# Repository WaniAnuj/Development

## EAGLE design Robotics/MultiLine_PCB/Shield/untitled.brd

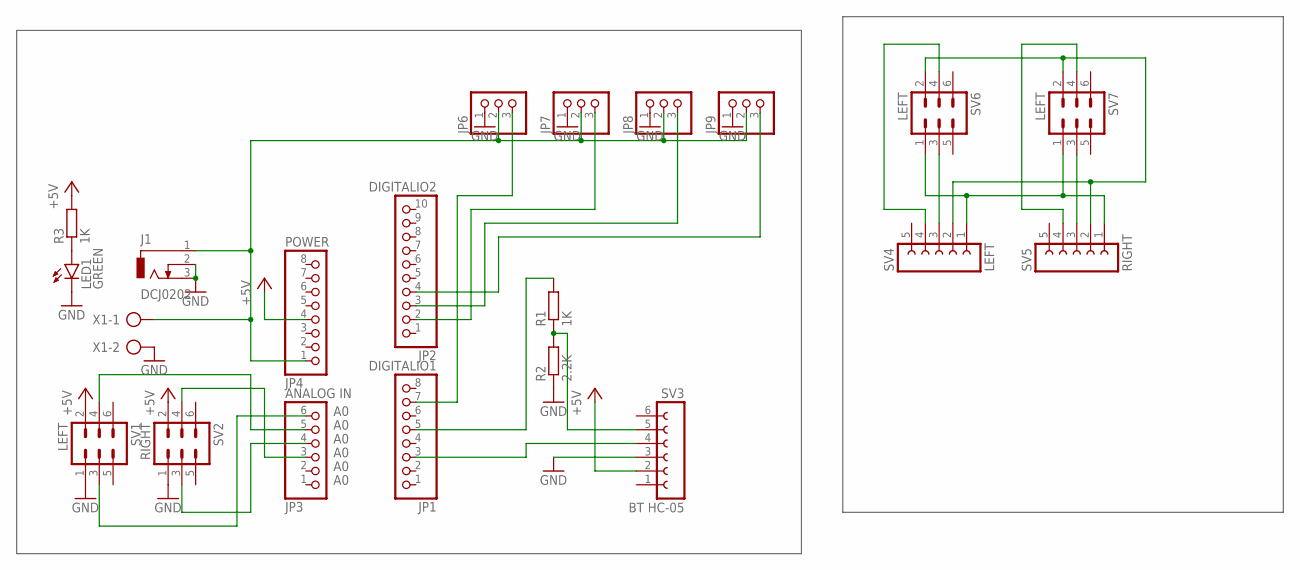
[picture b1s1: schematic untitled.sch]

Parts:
J1: DCJ0202
JP1: DIGITALIO1; 1X08
JP2: DIGITALIO2; 1X10
JP3: ANALOG IN; 1X06
JP4: POWER; 1X08
JP6, JP7, JP8, JP9: PINHD-1X3; 1X03
LED1: GREEN; LED3MM
R1, R3: 1K; 0207/10
R2: 2.2K; 0207/10
SV1, SV6, SV7: LEFT; ML6
SV2: RIGHT; ML6
SV3: BT HC-05; FE06W
SV4: LEFT; FE05W
SV5: RIGHT; FE05W
X1: AK300/2

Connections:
+5V: JP4.4, R3.2, SV1.2, SV2.2, SV3.2
GND: J1.2, J1.3, JP6.1, JP7.1, JP8.1, JP9.1, LED1.K (C), R2.1, SV1.1, SV2.1, SV3.3, X1.2
unnamed: JP1.3, SV3.4
unnamed: J1.1, JP4.1, JP6.2, JP7.2, JP8.2, JP9.2, X1.1
unnamed: R1.1, R2.2, SV3.5
unnamed: JP1.5, R1.2
unnamed: JP3.6, SV1.3
unnamed: JP1.7, JP6.3
unnamed: JP2.2, JP7.3
unnamed: JP2.3, JP8.3
unnamed: JP2.4, JP9.3
unnamed: JP3.5, SV1.4
unnamed: JP3.4, SV2.3
unnamed: JP3.3, SV2.4
unnamed: LED1.A, R3.1
unnamed: SV4.1, SV5.1, SV6.1, SV7.1
unnamed: SV4.2, SV5.2, SV6.2, SV7.2
unnamed: SV4.3, SV6.3
unnamed: SV4.4, SV6.4
unnamed: SV5.3, SV7.3
unnamed: SV5.4, SV7.4

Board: 2 copper layers, 21 parts (0 on the bottom side), 21 nets, no tracks yet.

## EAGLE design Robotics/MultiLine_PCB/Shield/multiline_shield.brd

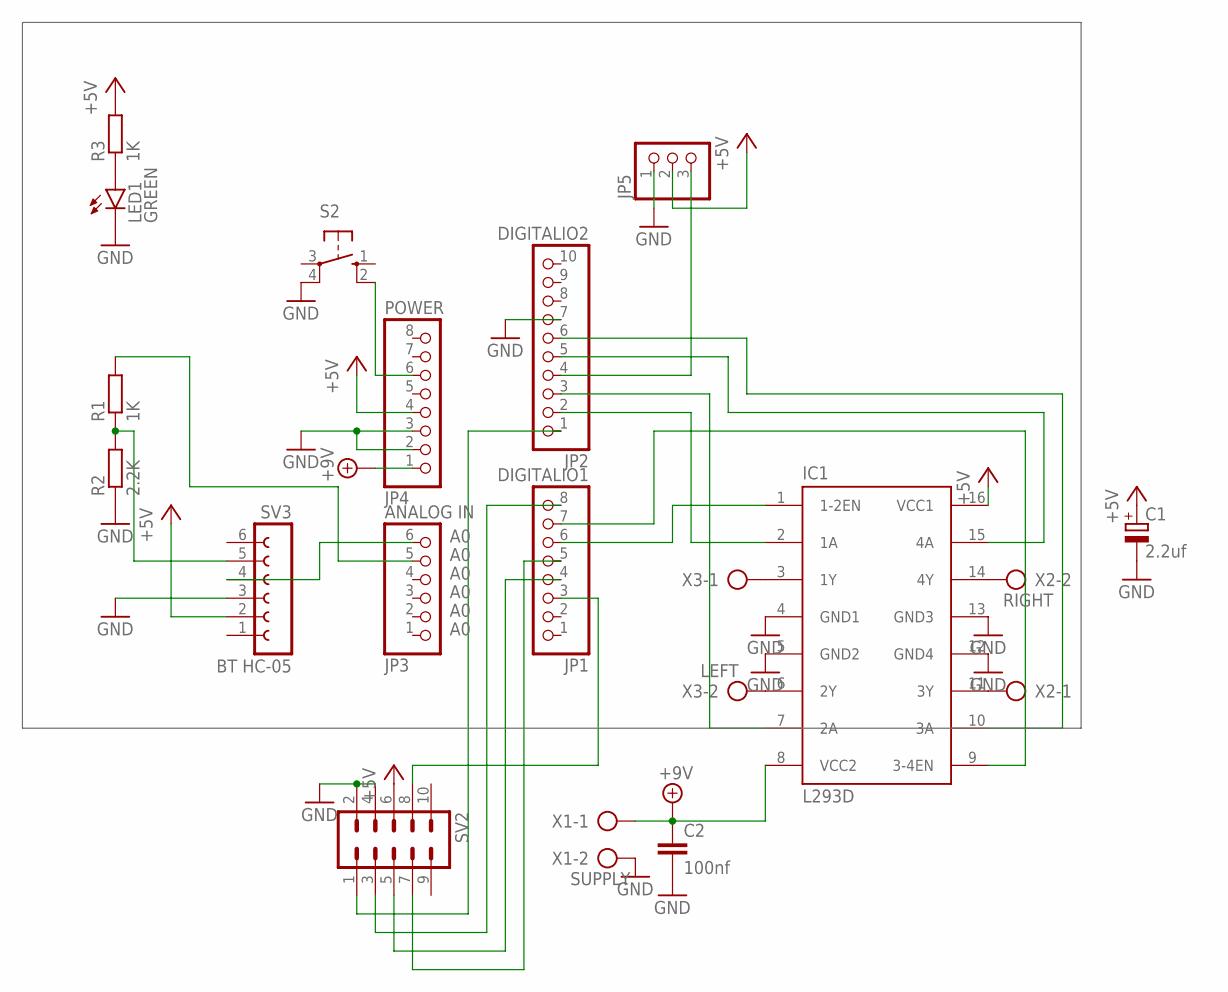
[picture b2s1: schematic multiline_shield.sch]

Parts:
C1: 2.2uf; E2,5-6
C2: 100nf; C025-025X050
IC1: L293D; DIL16
JP1: DIGITALIO1; 1X08
JP2: DIGITALIO2; 1X10
JP3: ANALOG IN; 1X06
JP4: POWER; 1X08
JP5: PINHD-1X3; 1X03
LED1: GREEN; LED3MM
R1, R3: 1K; 0207/10
R2: 2.2K; 0207/10
S2: 10-XX; B3F-10XX
SV2: ML10
SV3: BT HC-05; FE06
X1: SUPPLY; AK300/2
X2: RIGHT; AK300/2
X3: LEFT; AK300/2

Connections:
+5V: C1.+, IC1.16 (VCC1), JP4.4, JP5.2, R3.2, SV2.6, SV3.2
+9V: C2.1, IC1.8 (VCC2), JP4.1, X1.1
GND: C1.-, C2.2, IC1.4 (GND1), IC1.5 (GND2), IC1.12 (GND4), IC1.13 (GND3), JP2.7, JP4.2, JP4.3, JP5.1, LED1.K (C), R2.1, S2.4 (P1), SV2.2, SV2.4, SV3.3, X1.2
unnamed: JP3.6, SV3.4
unnamed: JP4.6, S2.2 (S1)
unnamed: R1.1, R2.2, SV3.5
unnamed: JP3.5, R1.2
unnamed: IC1.2 (1A), JP2.2
unnamed: JP2.4, JP5.3
unnamed: IC1.7 (2A), JP2.3
unnamed: IC1.1 (1-2EN), JP1.6
unnamed: IC1.15 (4A), JP2.5
unnamed: IC1.10 (3A), JP2.6
unnamed: IC1.9 (3-4EN), JP1.7
unnamed: IC1.11 (3Y), X2.1
unnamed: LED1.A, R3.1
unnamed: IC1.14 (4Y), X2.2
unnamed: IC1.3 (1Y), X3.1
unnamed: IC1.6 (2Y), X3.2
unnamed: JP2.1, SV2.1
unnamed: JP1.8, SV2.3
unnamed: JP1.4, SV2.5
unnamed: JP1.5, SV2.7
unnamed: JP1.3, SV2.8

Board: 2 copper layers, 18 parts (0 on the bottom side), 24 nets, no tracks yet.

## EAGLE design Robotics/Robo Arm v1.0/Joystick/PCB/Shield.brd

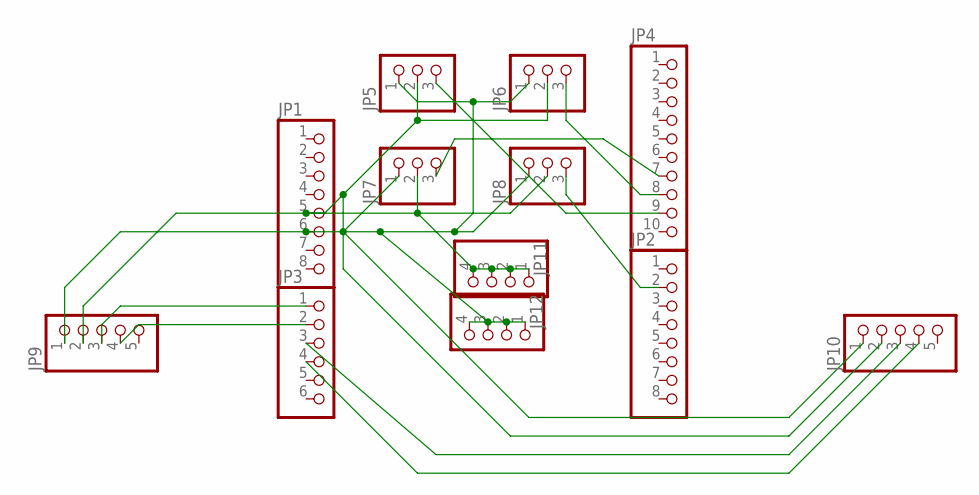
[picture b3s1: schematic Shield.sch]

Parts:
JP1, JP2: PINHD-1X8; 1X08
JP3: PINHD-1X6; 1X06
JP4: PINHD-1X10; 1X10
JP5, JP6, JP7, JP8: PINHD-1X3; 1X03
JP9, JP10: PINHD-1X5; 1X05
JP11, JP12: PINHD-1X4; 1X04

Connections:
GND: JP1.6, JP5.1, JP6.1, JP7.1, JP8.1, JP9.1, JP10.1, JP12.1, JP12.2, JP12.3, JP12.4
unnamed: JP1.5, JP5.2, JP6.2, JP7.2, JP8.2, JP9.2, JP10.2, JP11.1, JP11.2, JP11.3, JP11.4
unnamed: JP4.9, JP5.3
unnamed: JP3.1, JP9.3
unnamed: JP4.8, JP6.3
unnamed: JP3.2, JP9.4
unnamed: JP3.3, JP10.3
unnamed: JP3.4, JP10.4
unnamed: JP2.2, JP8.3
unnamed: JP4.7, JP7.3

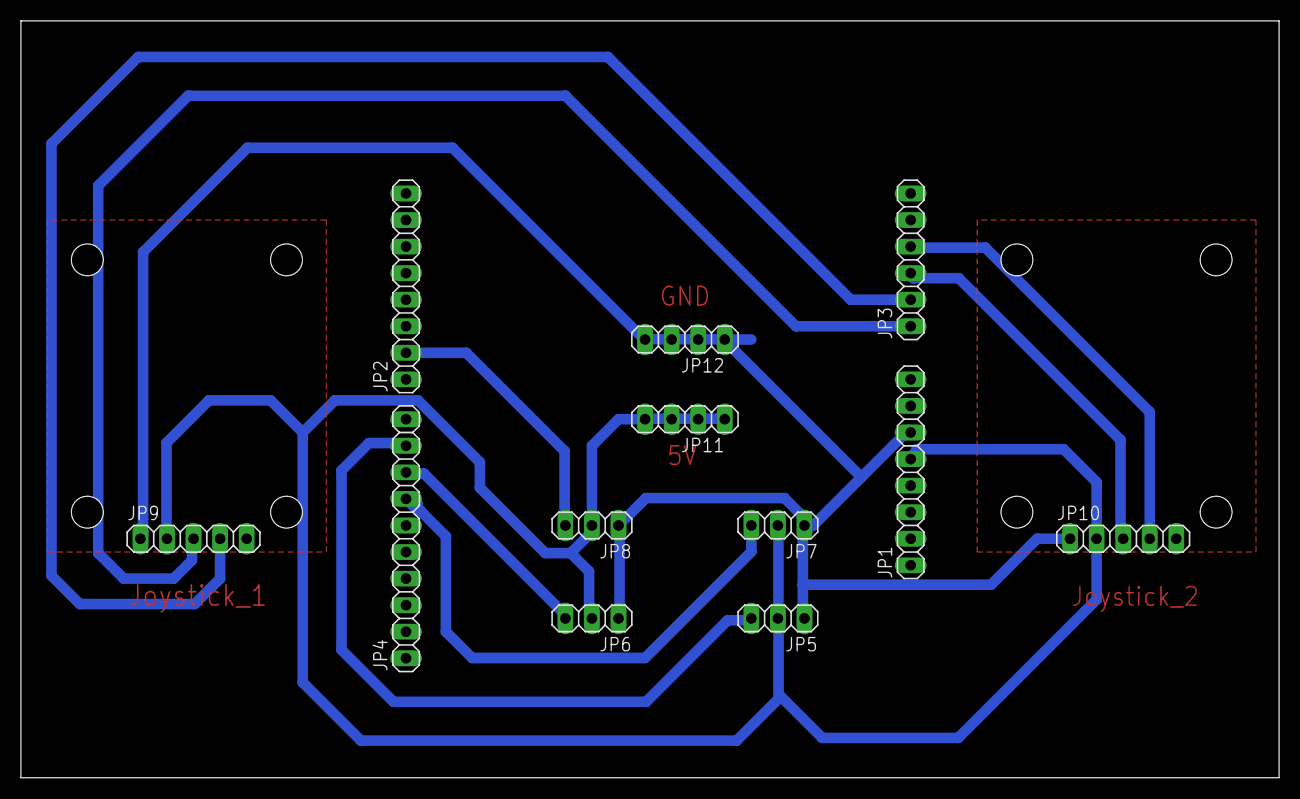
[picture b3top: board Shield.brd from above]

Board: 2 copper layers, 120.3 x 72.4 mm, 12 parts (0 on the bottom side), 10 nets.

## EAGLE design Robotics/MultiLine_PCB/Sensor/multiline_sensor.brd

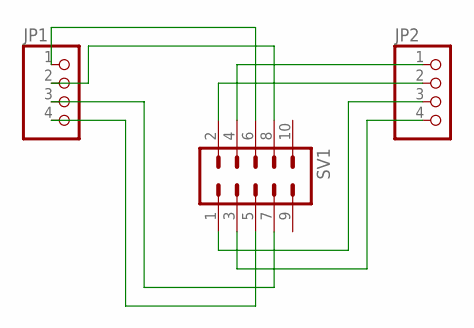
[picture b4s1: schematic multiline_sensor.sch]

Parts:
JP1, JP2: PINHD-1X4; 1X04
SV1: ML10

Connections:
unnamed: JP2.4, SV1.3
unnamed: JP2.3, SV1.1
unnamed: JP2.2, SV1.2
unnamed: JP2.1, SV1.4
unnamed: JP1.1, SV1.6
unnamed: JP1.2, SV1.8
unnamed: JP1.3, SV1.7
unnamed: JP1.4, SV1.5

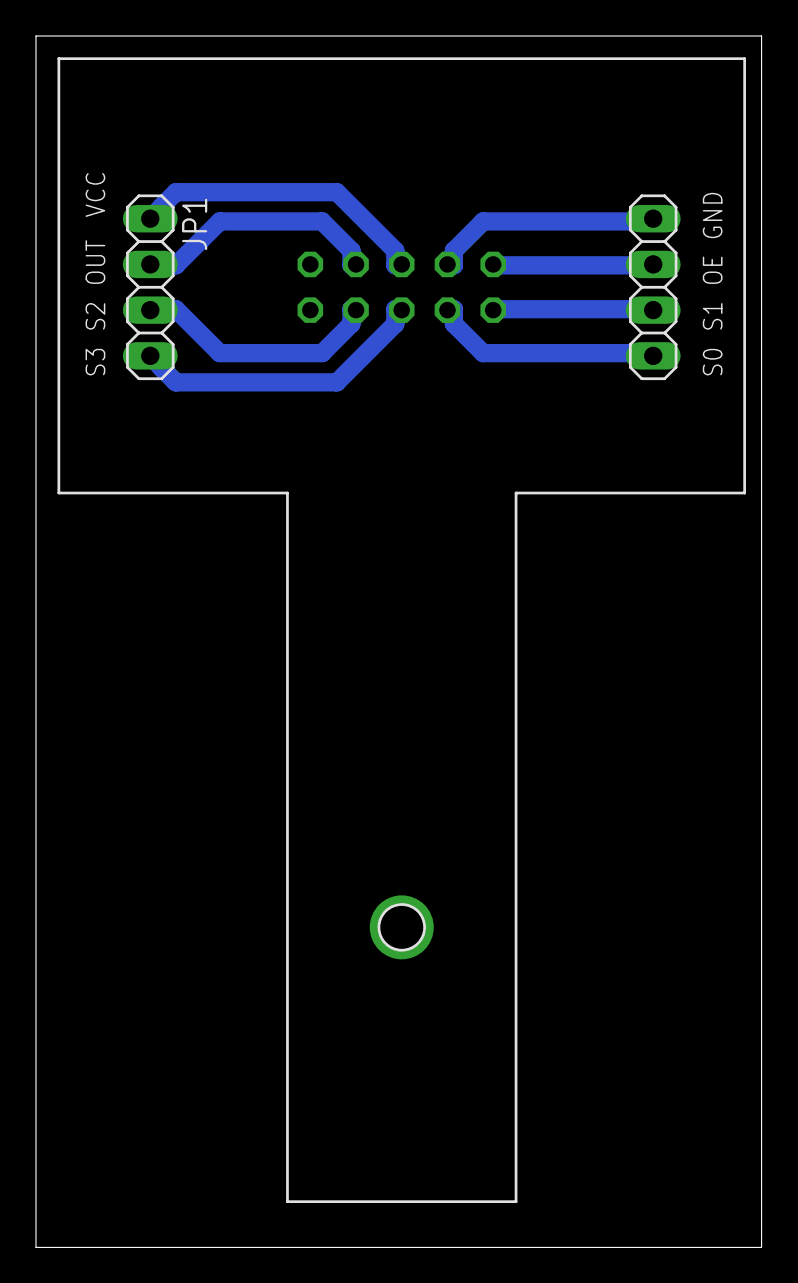
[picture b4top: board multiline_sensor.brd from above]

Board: 2 copper layers, 40.3 x 67.3 mm, 3 parts (1 on the bottom side), 8 nets.

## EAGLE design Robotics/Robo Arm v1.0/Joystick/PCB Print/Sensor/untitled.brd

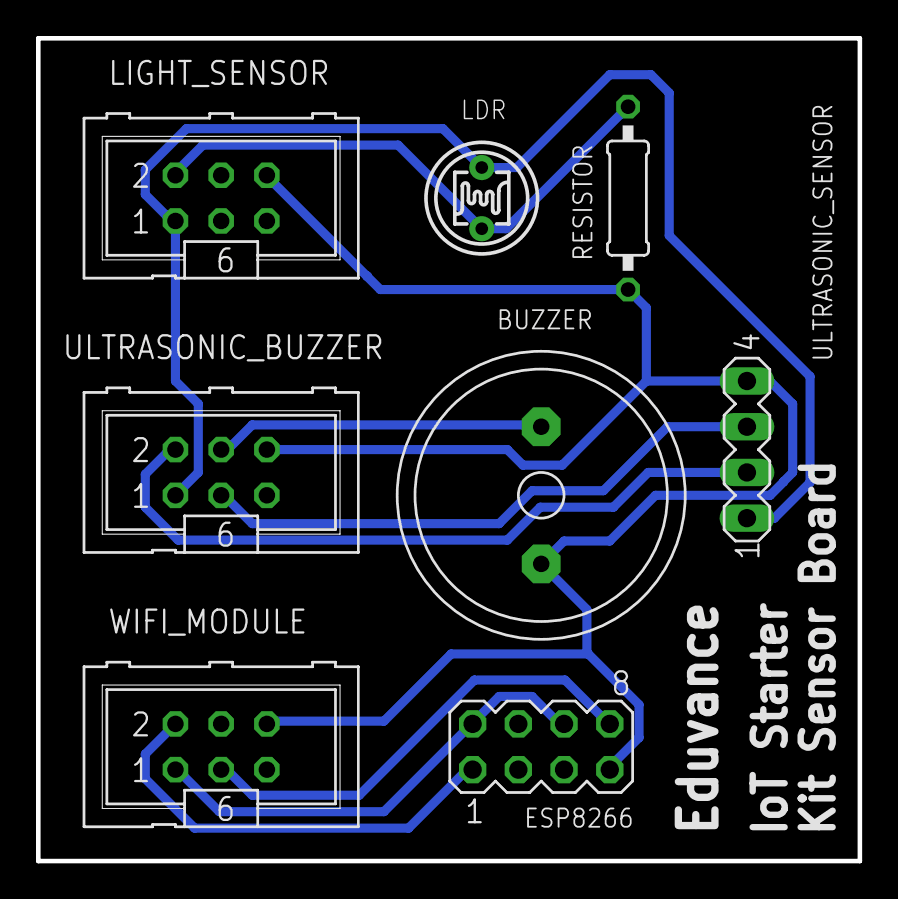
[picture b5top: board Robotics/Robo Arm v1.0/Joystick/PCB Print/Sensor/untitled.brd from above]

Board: 2 copper layers, 45.6 x 45.7 mm, 8 parts (0 on the bottom side), 9 nets.

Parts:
BUZZER: BUZZER; F/QMB
ESP8266: MA04-2
LDR: T0-46-A10XX
LIGHT_SENSOR: ML6
RESISTOR: 0207/10
ULTRASONIC_BUZZER: ML6
ULTRASONIC_SENSOR: MA04-1
WIFI_MODULE: ML6

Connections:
3V3: ESP8266.2, ESP8266.6, WIFI_MODULE.1
5V: LDR.1, LIGHT_SENSOR.1, ULTRASONIC_BUZZER.1, ULTRASONIC_SENSOR.1
BUZ: BUZZER.+, ULTRASONIC_BUZZER.4
ECHO: ULTRASONIC_BUZZER.3, ULTRASONIC_SENSOR.3
GND: BUZZER.-, ESP8266.7, LIGHT_SENSOR.6, RESISTOR.1, ULTRASONIC_BUZZER.6, ULTRASONIC_SENSOR.4, WIFI_MODULE.6
RX: ESP8266.1, WIFI_MODULE.2
SG: LDR.2, LIGHT_SENSOR.2, RESISTOR.2
TRIG: ULTRASONIC_BUZZER.2, ULTRASONIC_SENSOR.2
TX: ESP8266.8, WIFI_MODULE.3

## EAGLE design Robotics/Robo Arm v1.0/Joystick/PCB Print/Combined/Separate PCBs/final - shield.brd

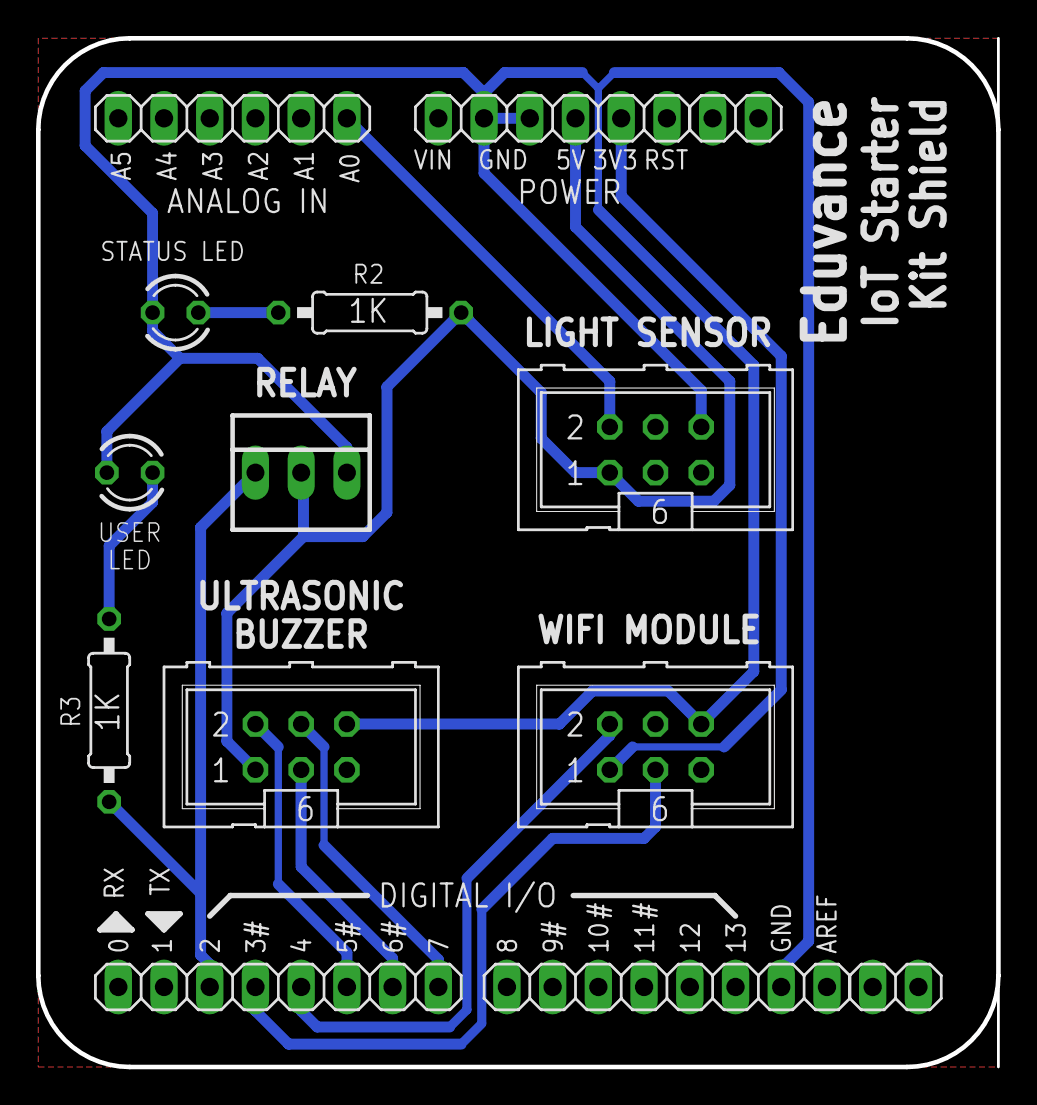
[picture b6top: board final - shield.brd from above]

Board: 2 copper layers, 53.3 x 57.1 mm, 14 parts (0 on the bottom side), 4 nets.

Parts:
AD: 1X06
IOH: 1X08
IOL: 1X08
LED: USER LED; LED3MM
LIGHT_SENSOR2: LIGHT SENSOR; ML6
POWER: 1X06
R2, R3: 1K; 0207/10
RELAY: 22-23-2031
STATUS_LED: STATUS LED; LED3MM
ULTRASONIC_BUZZER2: ULTRASONIC BUZZER; ML6
WIFI_MODULE2: WIFI MODULE; ML6
_: 1X02
__: 1X02

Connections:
GND2: IOH.7, LED.K, POWER.4, POWER.5, RELAY.3, STATUS_LED.K
unnamed: POWER.3, RELAY.2
unnamed: IOL.3, R3.2, RELAY.1
S$1: LED.A, R3.1

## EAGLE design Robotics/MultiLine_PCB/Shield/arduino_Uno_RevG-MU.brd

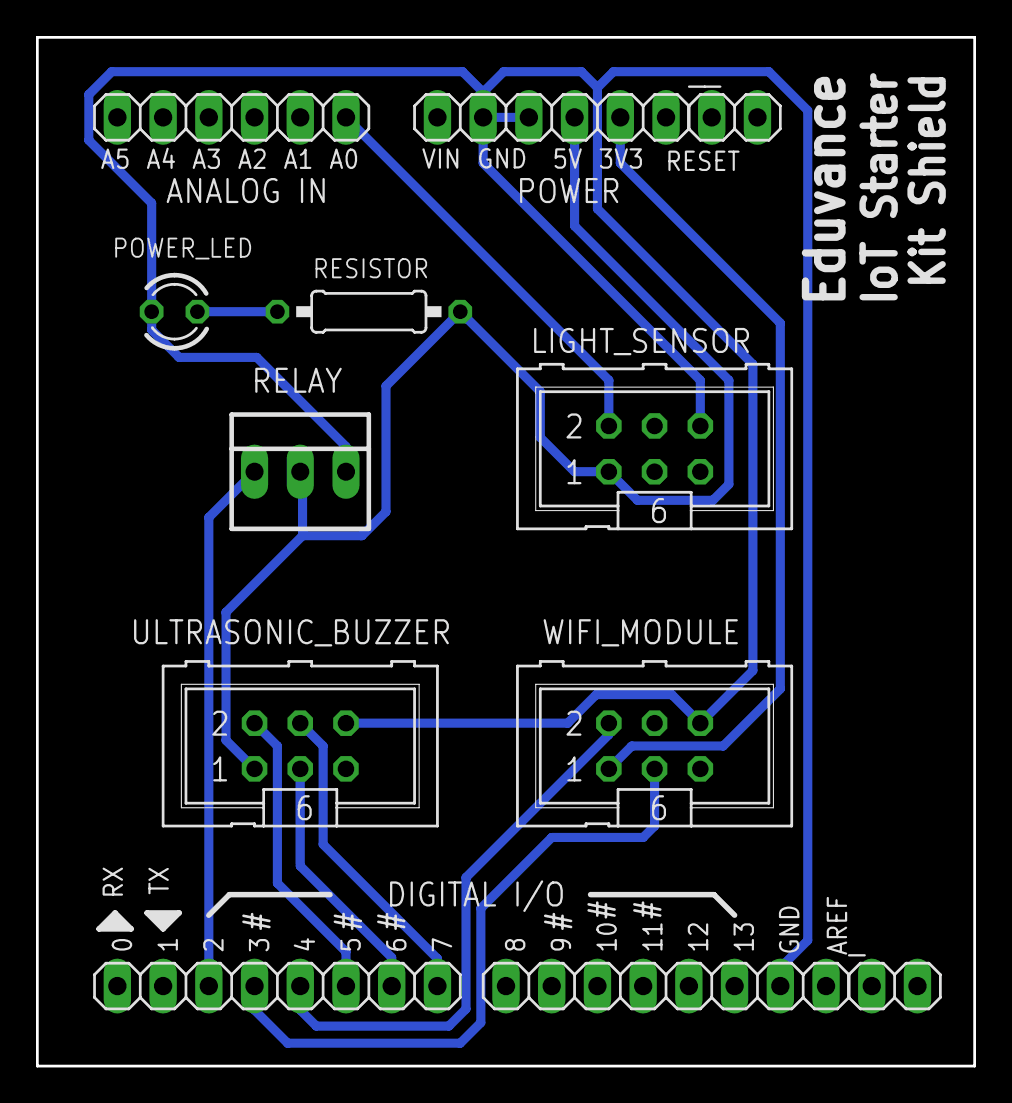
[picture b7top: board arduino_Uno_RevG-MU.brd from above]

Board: 2 copper layers, 52.1 x 57.1 mm, 12 parts (0 on the bottom side), 11 nets.

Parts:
AD: 1X06
IOH: 1X08
IOL: 1X08
LIGHT_SENSOR: ML6
POWER: 1X06
POWER_LED: LED3MM
RELAY: 22-23-2031
RESISTOR: 330E; 0207/10
ULTRASONIC_BUZZER: ML6
WIFI_MODULE: ML6
_: 1X02
__: 1X02

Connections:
GND: IOH.7, LIGHT_SENSOR.6, POWER.4, POWER.5, POWER_LED.K, RELAY.3, ULTRASONIC_BUZZER.6, WIFI_MODULE.6
unnamed: LIGHT_SENSOR.1, POWER.3, RELAY.2, RESISTOR.1, ULTRASONIC_BUZZER.1
unnamed: AD.1, LIGHT_SENSOR.2
unnamed: IOL.6, ULTRASONIC_BUZZER.2
unnamed: IOL.7, ULTRASONIC_BUZZER.3
unnamed: IOL.8, ULTRASONIC_BUZZER.4
unnamed: POWER.2, WIFI_MODULE.1
unnamed: IOL.4, WIFI_MODULE.3
unnamed: IOL.5, WIFI_MODULE.2
unnamed: POWER_LED.A, RESISTOR.2
unnamed: IOL.3, RELAY.1

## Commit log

2020-09-10 updated robo arm v5
2020-10-10 Added robo arm integrated joystick control and new versions of robo car
2020-10-12 Added RoboArm library but needs to be tested on actual hardware
2020-10-27 New version for robotic arm functioning, hex file and x loader
2020-10-28 Rectified the Sample mode functioning of robotic arm and added its hex file
2021-04-05 Added New IoT Lab files
2021-04-05 All lora and other arduino files with respective lib
2021-04-05 IoT simulator added
2021-04-29 BLE indoor tracking scripts and IoTKit programs added
2021-05-26 Made a few changes in BLE tracking and IoT Smartbin LoRa, Added new javascript for smartbin graph display on a webpage
